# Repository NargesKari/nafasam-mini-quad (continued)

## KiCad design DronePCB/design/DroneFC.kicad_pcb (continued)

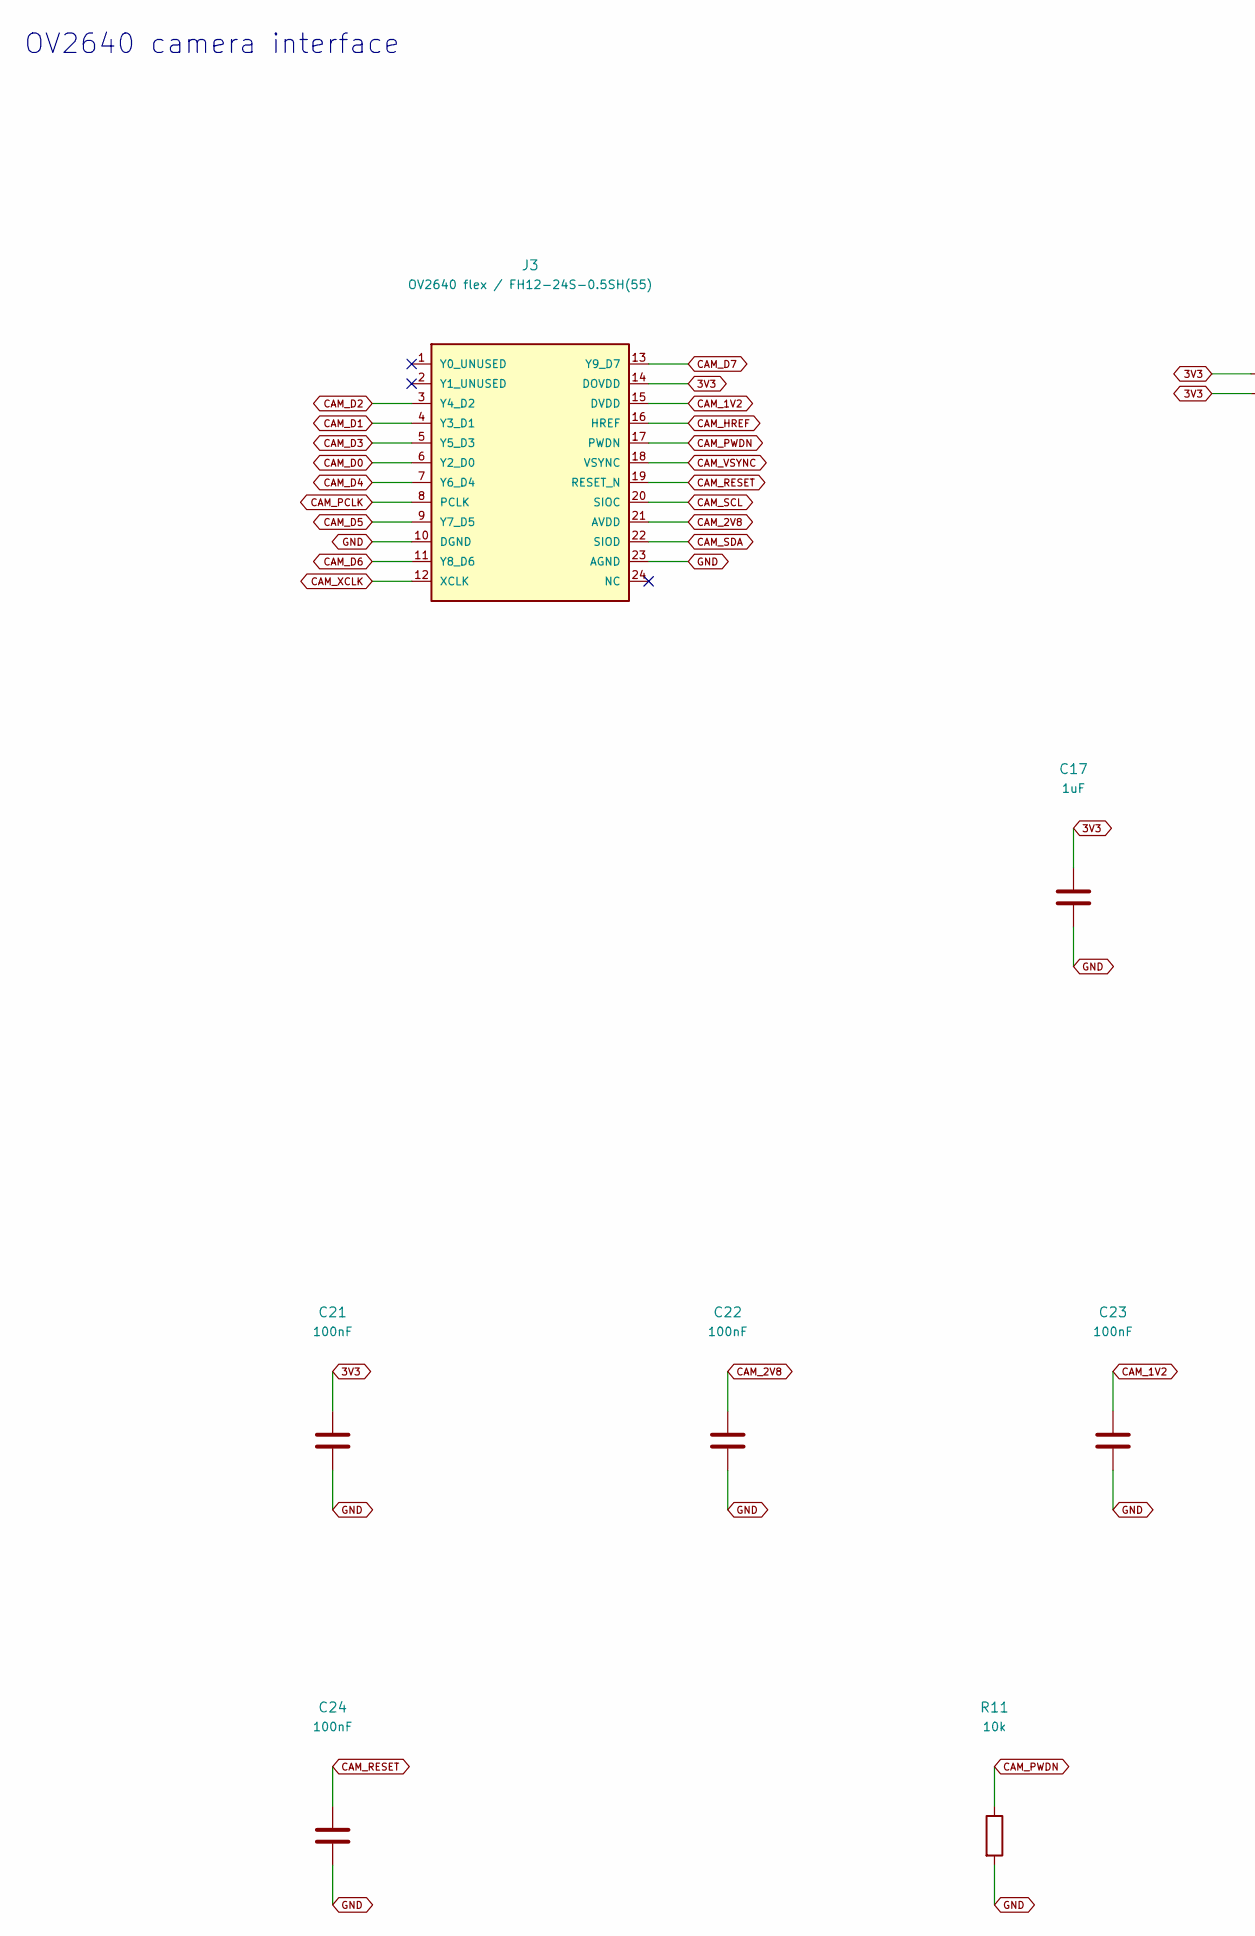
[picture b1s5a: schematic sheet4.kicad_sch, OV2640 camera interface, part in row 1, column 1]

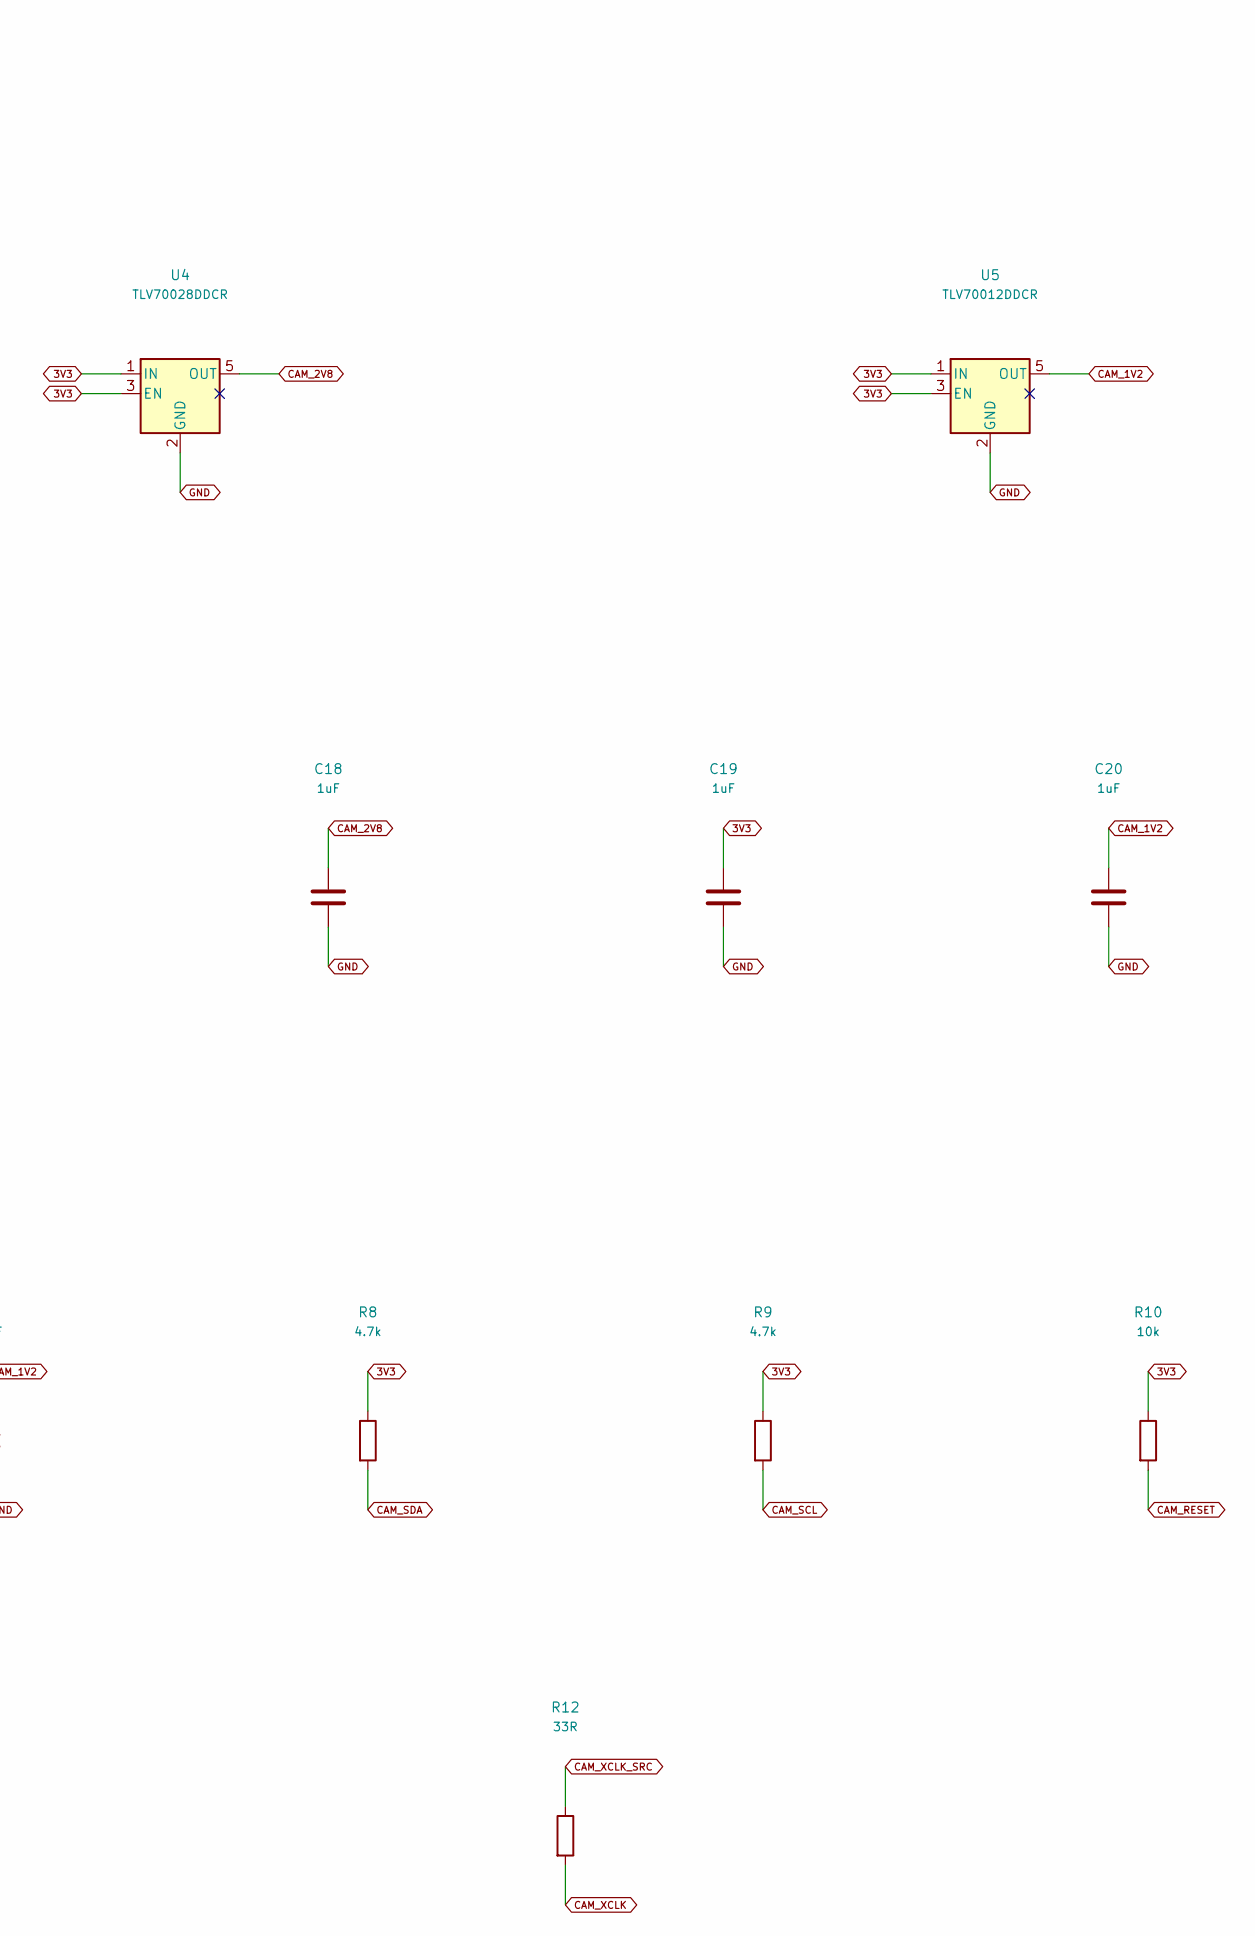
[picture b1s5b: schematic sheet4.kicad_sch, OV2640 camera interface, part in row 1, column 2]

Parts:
C17, C18, C19, C20: 1uF; C_0402_1005Metric
C21, C22, C23, C24: 100nF; C_0402_1005Metric
J3: OV2640 flex / FH12-24S-0.5SH(55); Hirose_FH12-24S-0.5SH_1x24-1MP_P0.50mm_Horizontal
R8, R9: 4.7k; R_0402_1005Metric
R10, R11: 10k; R_0402_1005Metric
R12: 33R; R_0402_1005Metric
U4: TLV70028DDCR; SOT-23-5
U5: TLV70012DDCR; SOT-23-5

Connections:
3V3: C17.1, C19.1, C21.1, J3.14 (DOVDD), R8.1, R9.1, R10.1, U4.1 (IN), U4.3 (EN), U5.1 (IN), U5.3 (EN); also elsewhere on the board
CAM_1V2: C20.1, C23.1, J3.15 (DVDD), U5.5 (OUT)
CAM_2V8: C18.1, C22.1, J3.21 (AVDD), U4.5 (OUT)
CAM_D0: J3.6 (Y2_D0); also elsewhere on the board
CAM_D1: J3.4 (Y3_D1); also elsewhere on the board
CAM_D2: J3.3 (Y4_D2); also elsewhere on the board
CAM_D3: J3.5 (Y5_D3); also elsewhere on the board
CAM_D4: J3.7 (Y6_D4); also elsewhere on the board
CAM_D5: J3.9 (Y7_D5); also elsewhere on the board
CAM_D6: J3.11 (Y8_D6); also elsewhere on the board
CAM_D7: J3.13 (Y9_D7); also elsewhere on the board
CAM_HREF: J3.16 (HREF); also elsewhere on the board
CAM_PCLK: J3.8 (PCLK); also elsewhere on the board
CAM_PWDN: J3.17 (PWDN), R11.1; also elsewhere on the board
CAM_RESET: C24.1, J3.19 (RESET_N), R10.2
CAM_SCL: J3.20 (SIOC), R9.2; also elsewhere on the board
CAM_SDA: J3.22 (SIOD), R8.2; also elsewhere on the board
CAM_VSYNC: J3.18 (VSYNC); also elsewhere on the board
CAM_XCLK: J3.12 (XCLK), R12.2
CAM_XCLK_SRC: R12.1; also elsewhere on the board
GND: C17.2, C18.2, C19.2, C20.2, C21.2, C22.2, C23.2, C24.2, J3.10 (DGND), J3.23 (AGND), R11.2, U4.2 (GND), U5.2 (GND); also elsewhere on the board

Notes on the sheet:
OV2640 camera interface

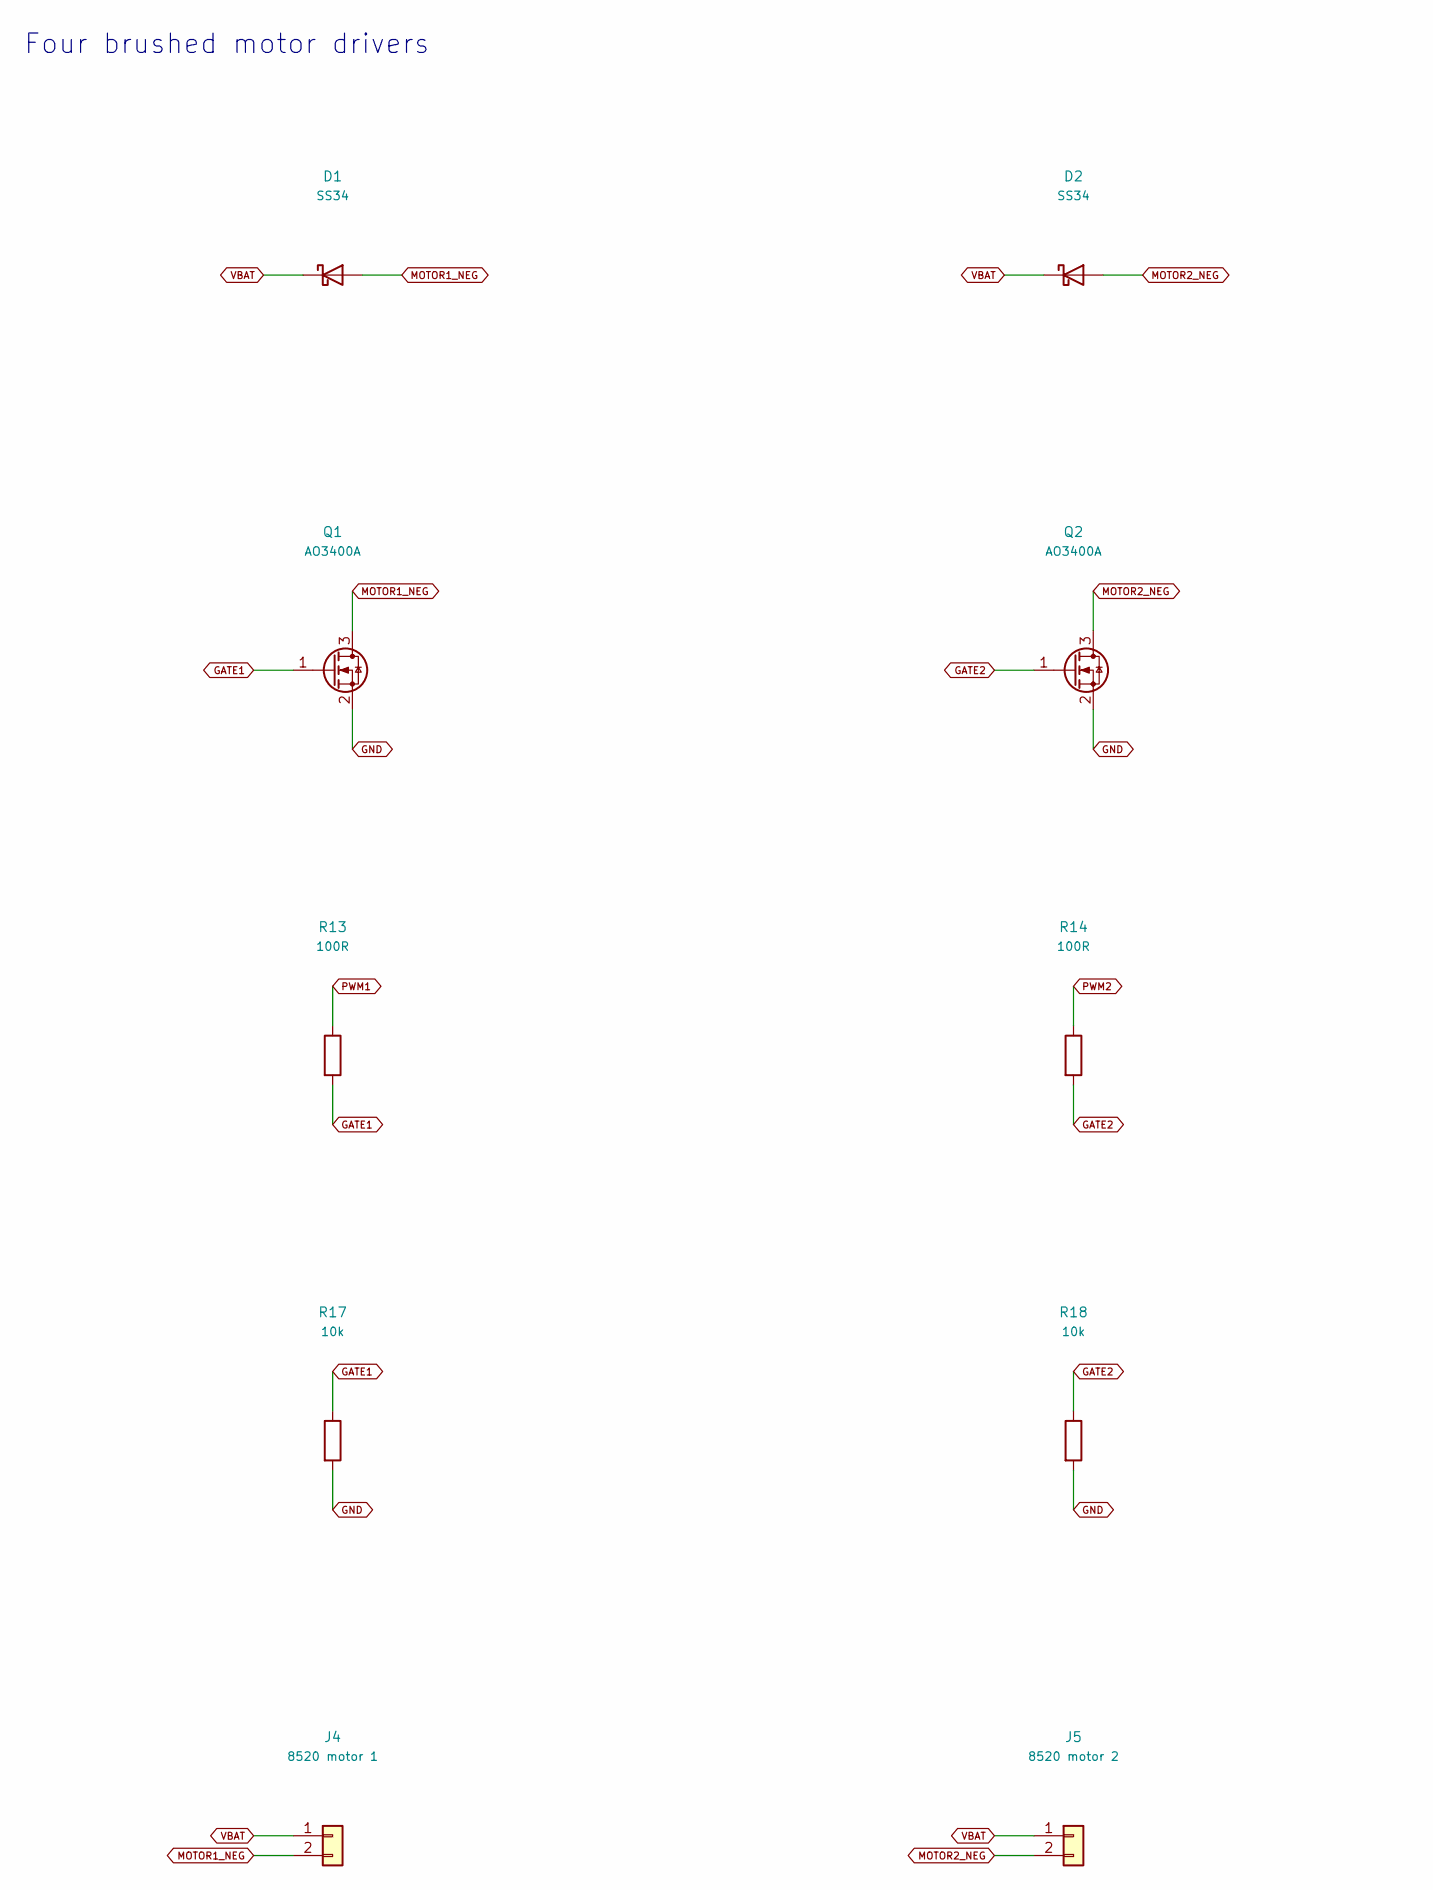
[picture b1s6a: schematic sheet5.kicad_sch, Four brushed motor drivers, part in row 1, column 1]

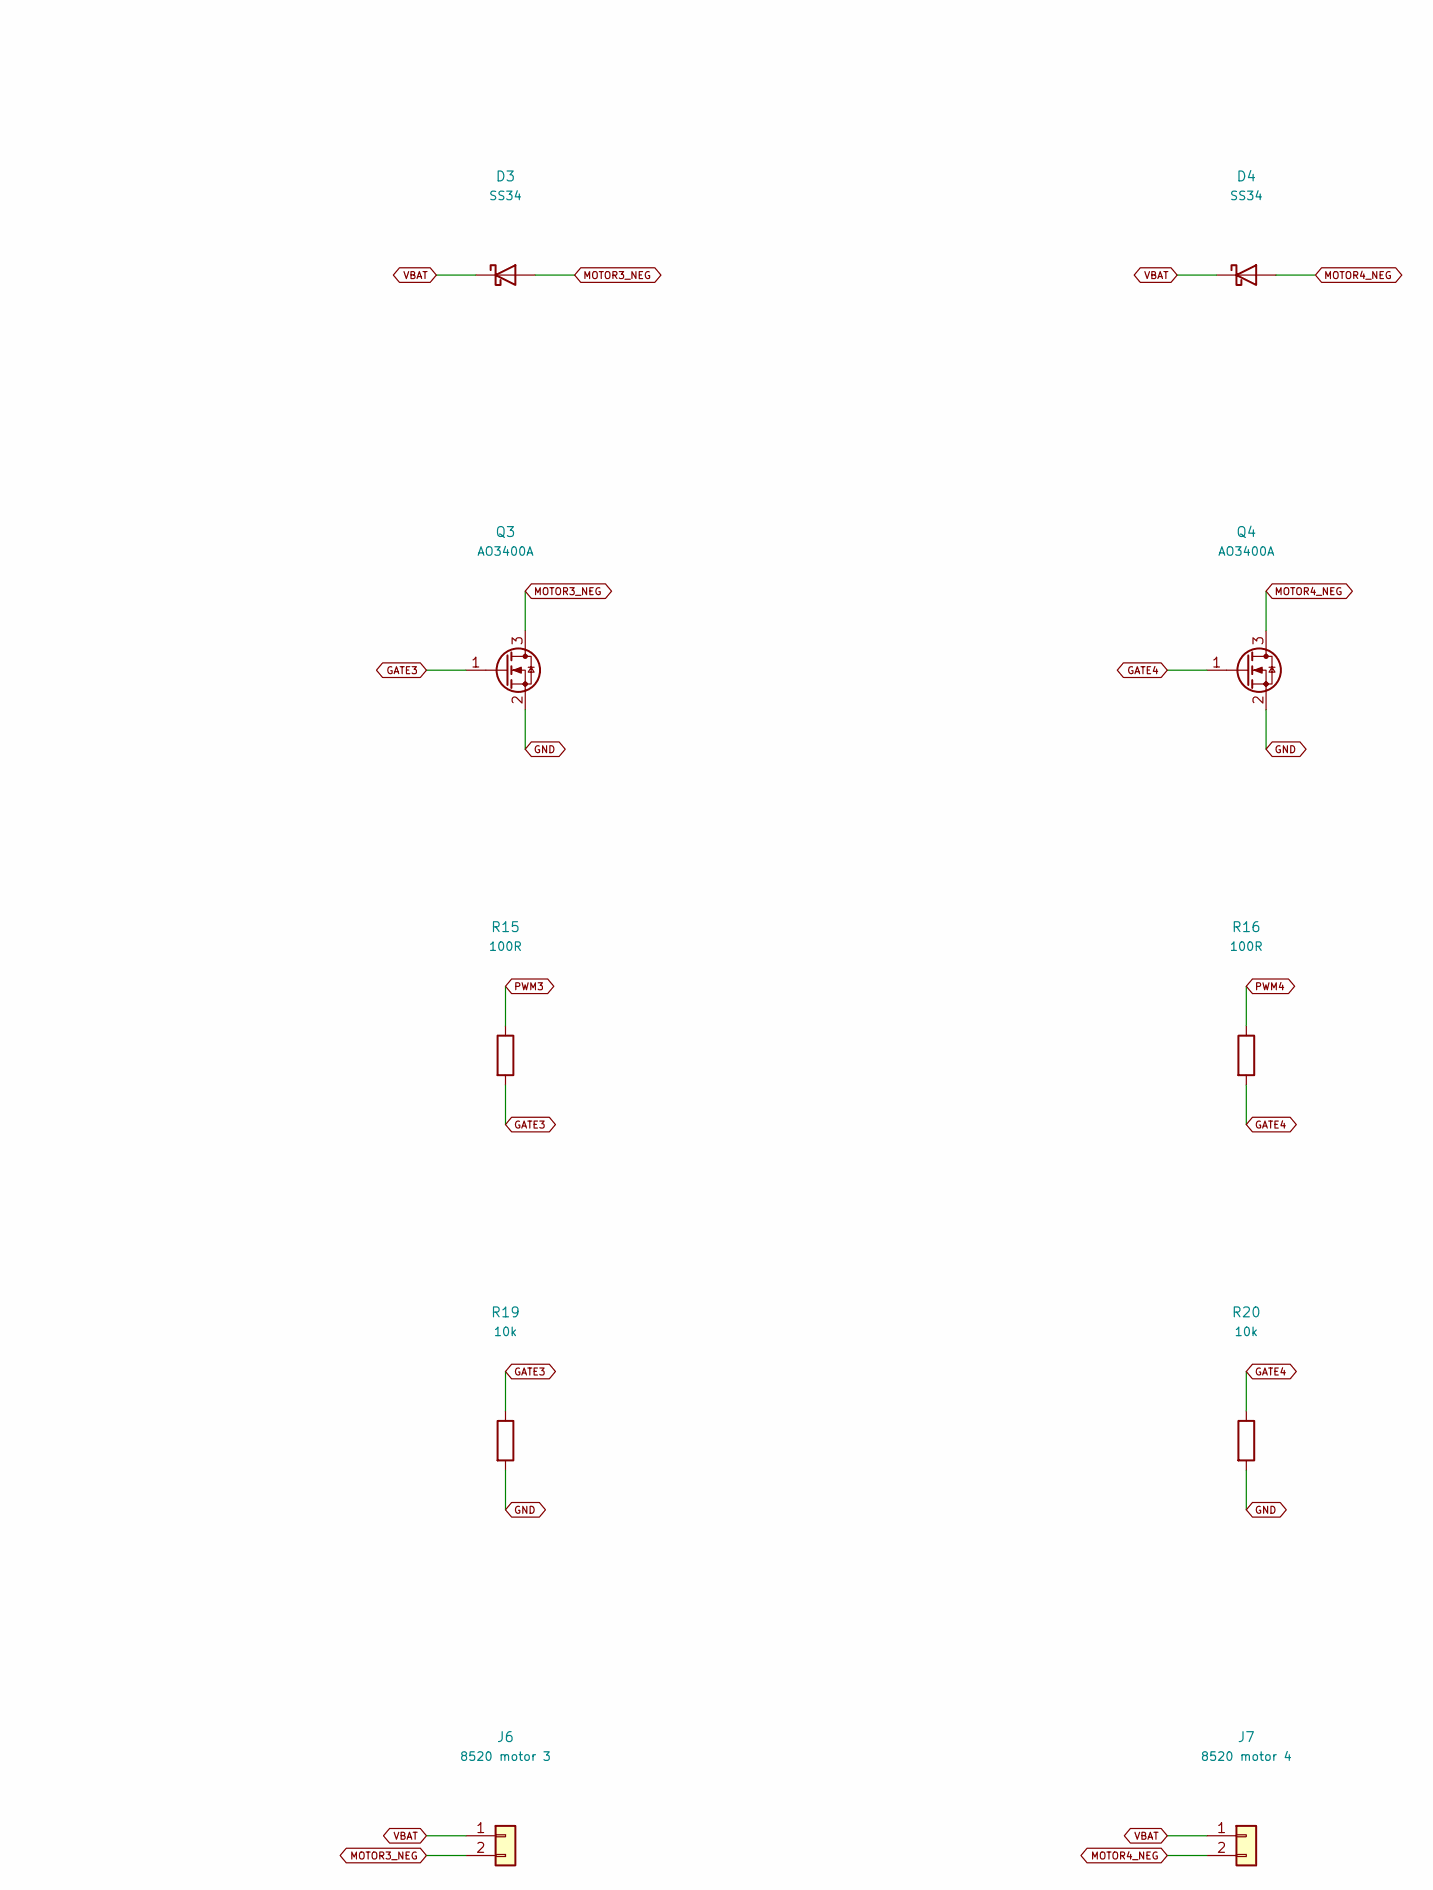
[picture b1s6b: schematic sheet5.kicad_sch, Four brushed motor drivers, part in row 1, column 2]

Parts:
D1, D2, D3, D4: SS34; D_SMA
J4: 8520 motor 1; Motor_2
J5: 8520 motor 2; Motor_2
J6: 8520 motor 3; Motor_2
J7: 8520 motor 4; Motor_2
Q1, Q2, Q3, Q4: AO3400A; SOT-23
R13, R14, R15, R16: 100R; R_0402_1005Metric
R17, R18, R19, R20: 10k; R_0402_1005Metric

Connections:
GATE1: Q1.1 (G), R13.2, R17.1
GATE2: Q2.1 (G), R14.2, R18.1
GATE3: Q3.1 (G), R15.2, R19.1
GATE4: Q4.1 (G), R16.2, R20.1
GND: Q1.2 (S), Q2.2 (S), Q3.2 (S), Q4.2 (S), R17.2, R18.2, R19.2, R20.2; also elsewhere on the board
MOTOR1_NEG: D1.2 (A), J4.2, Q1.3 (D)
MOTOR2_NEG: D2.2 (A), J5.2, Q2.3 (D)
MOTOR3_NEG: D3.2 (A), J6.2, Q3.3 (D)
MOTOR4_NEG: D4.2 (A), J7.2, Q4.3 (D)
PWM1: R13.1; also elsewhere on the board
PWM2: R14.1; also elsewhere on the board
PWM3: R15.1; also elsewhere on the board
PWM4: R16.1; also elsewhere on the board
VBAT: D1.1 (K), D2.1 (K), D3.1 (K), D4.1 (K), J4.1, J5.1, J6.1, J7.1; also elsewhere on the board

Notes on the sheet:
Four brushed motor drivers

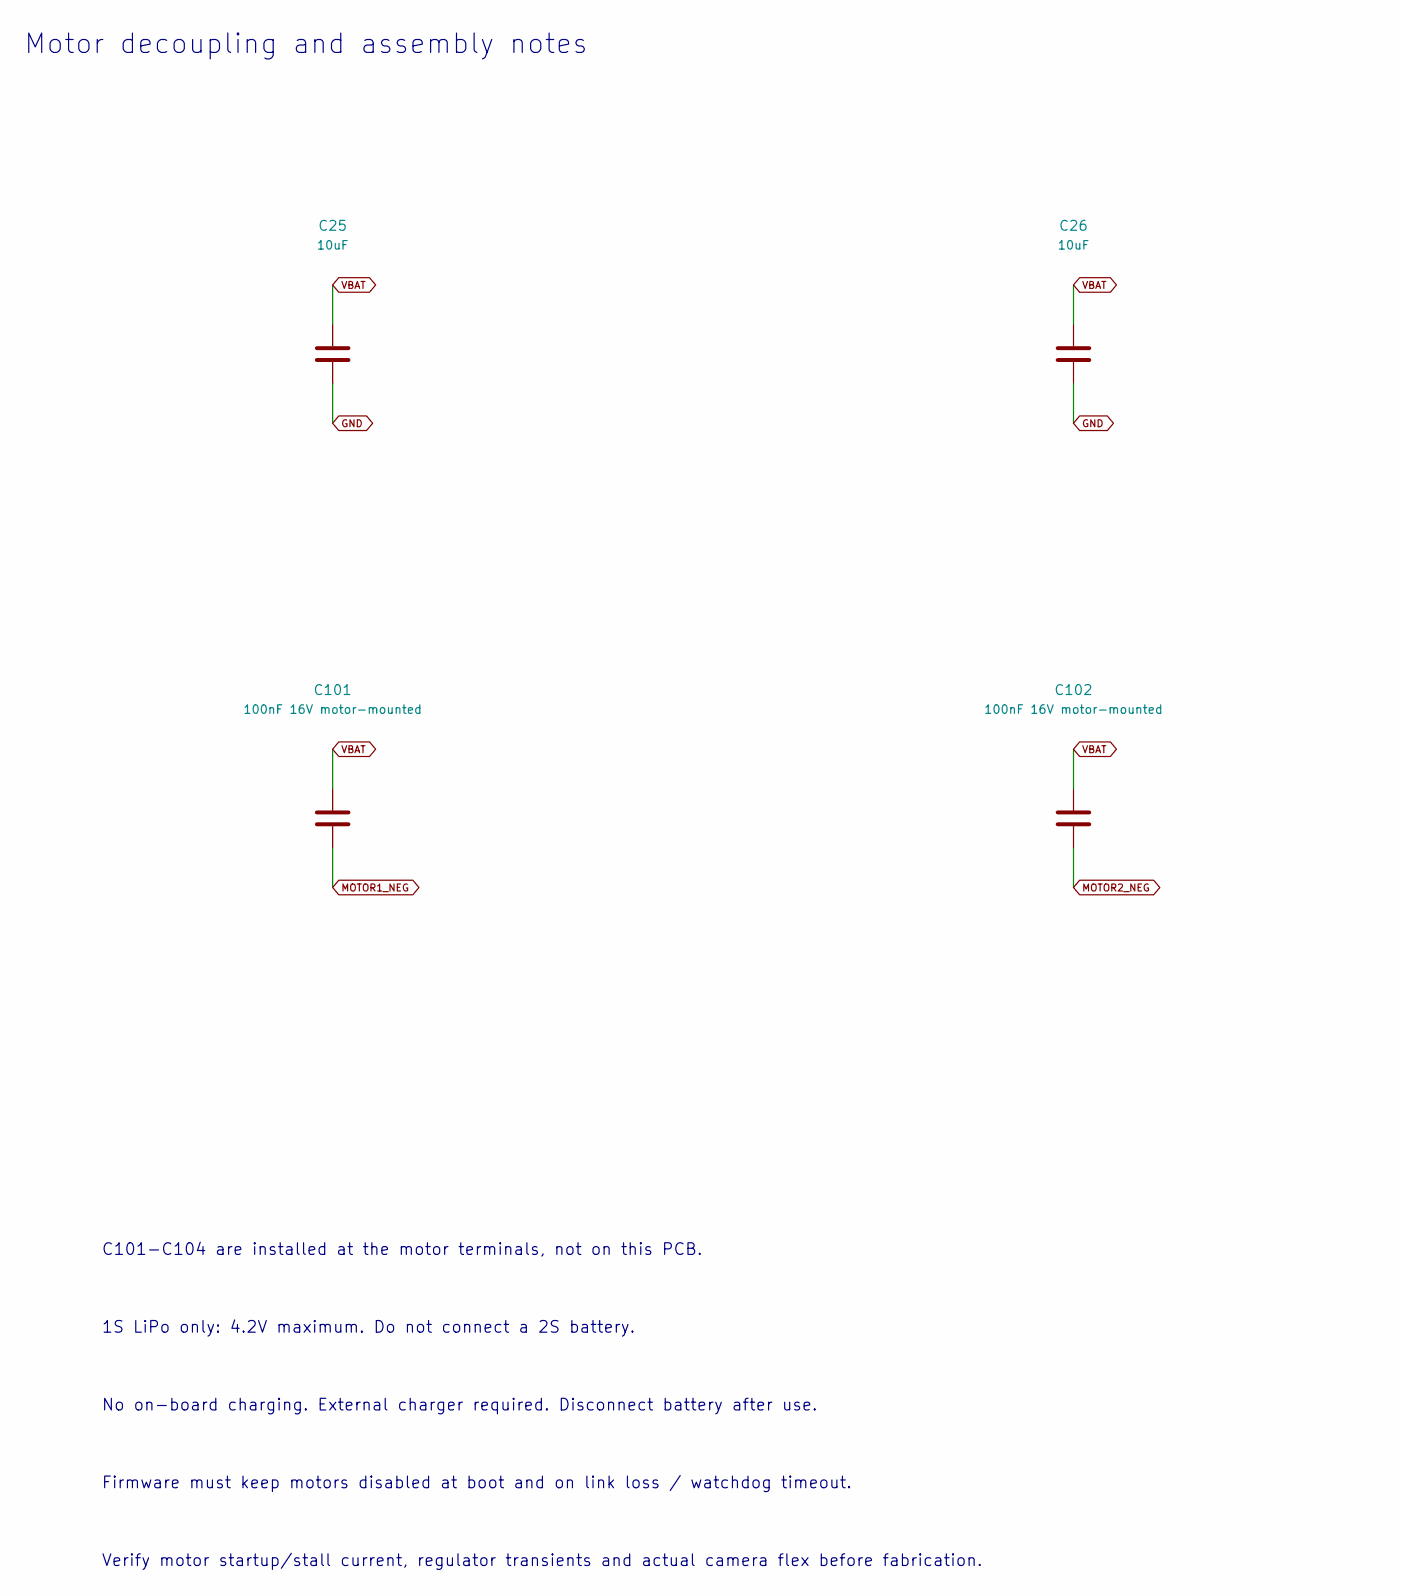
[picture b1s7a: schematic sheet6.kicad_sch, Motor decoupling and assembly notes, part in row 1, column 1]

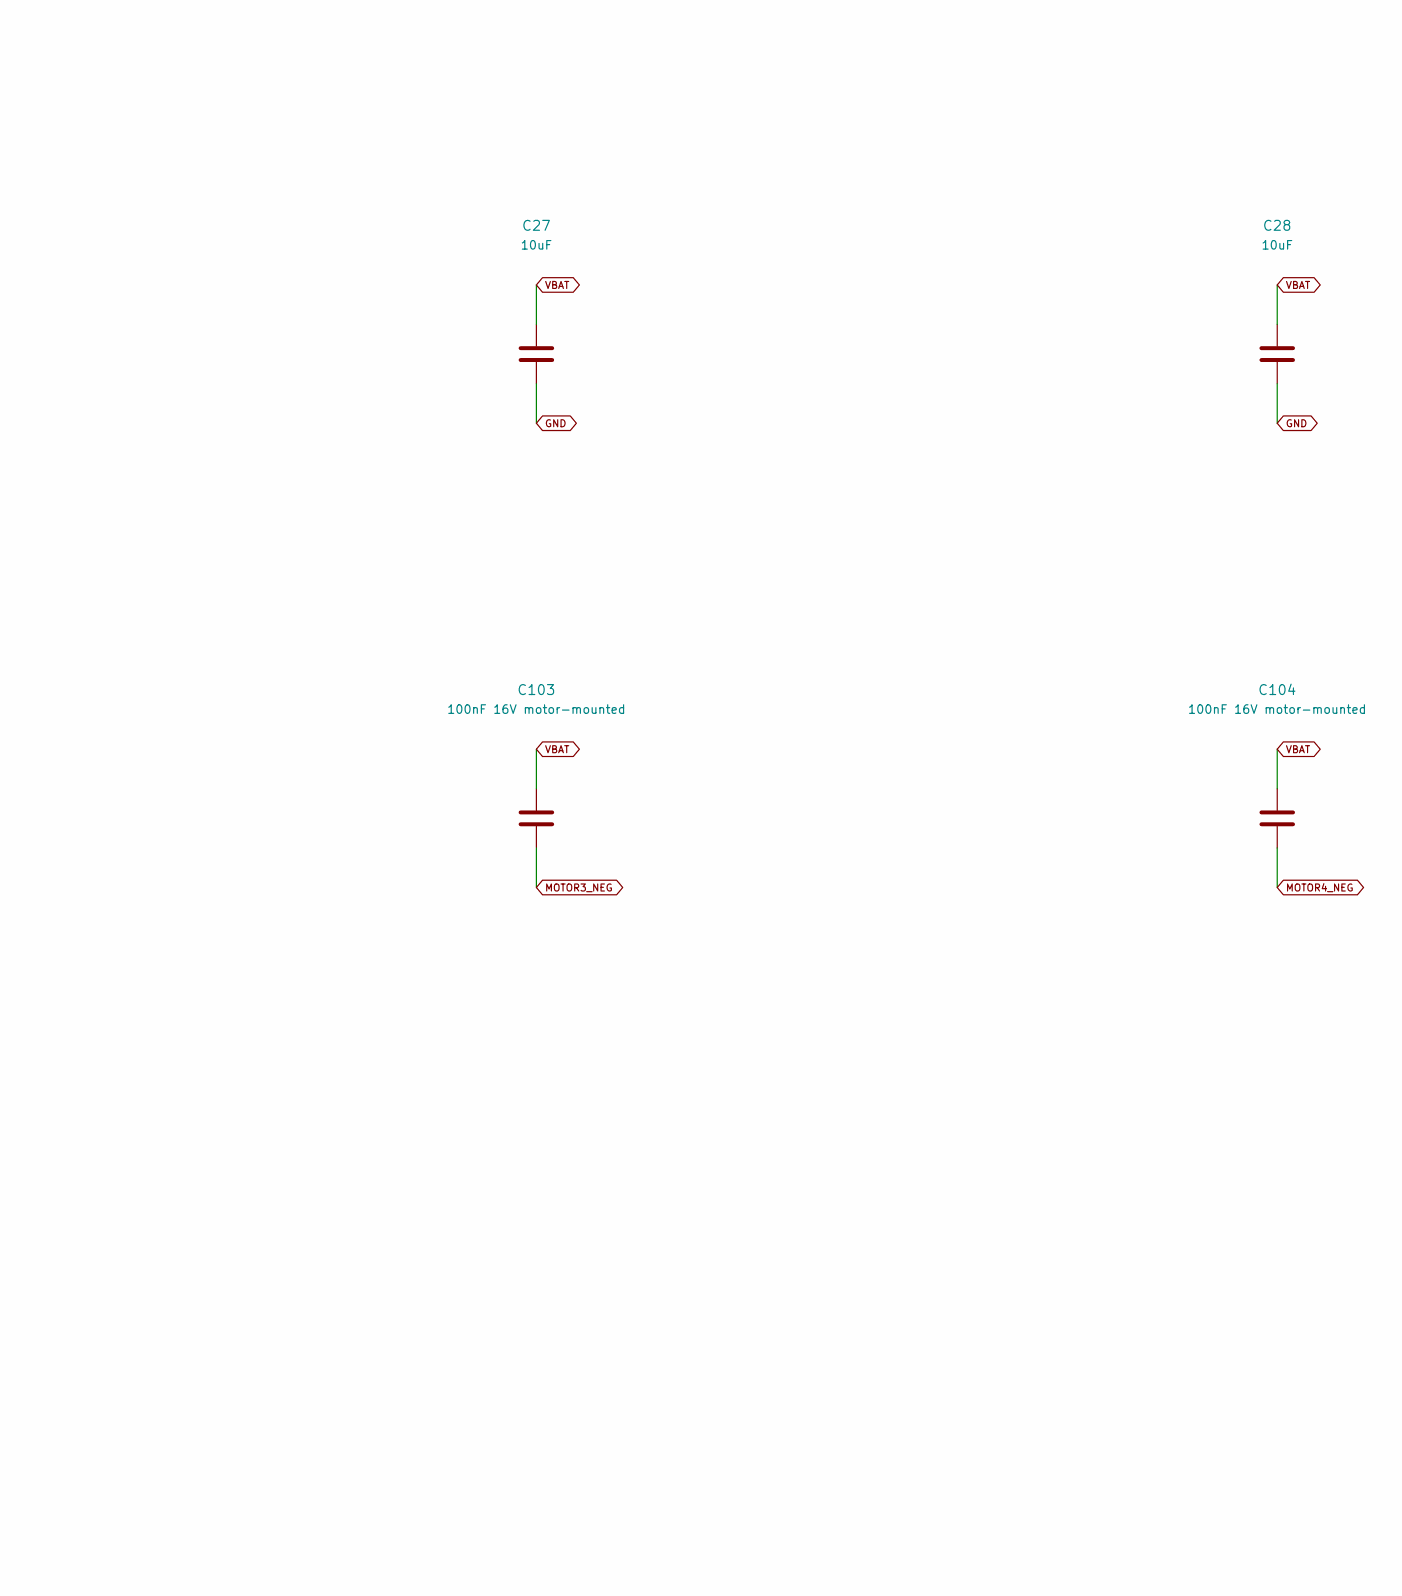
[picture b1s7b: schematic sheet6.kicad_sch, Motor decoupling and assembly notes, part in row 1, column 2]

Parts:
C25, C26, C27, C28: 10uF; C_0603_1608Metric
C101, C102, C103, C104: 100nF 16V motor-mounted

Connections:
GND: C25.2, C26.2, C27.2, C28.2; also elsewhere on the board
VBAT: C25.1, C26.1, C27.1, C28.1, C101.1, C102.1, C103.1, C104.1; also elsewhere on the board

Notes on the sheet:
Motor decoupling and assembly notes
C101-C104 are installed at the motor terminals, not on this PCB.
1S LiPo only: 4.2V maximum. Do not connect a 2S battery.
No on-board charging. External charger required. Disconnect battery after use.
Firmware must keep motors disabled at boot and on link loss / watchdog timeout.
Verify motor startup/stall current, regulator transients and actual camera flex before fabrication.

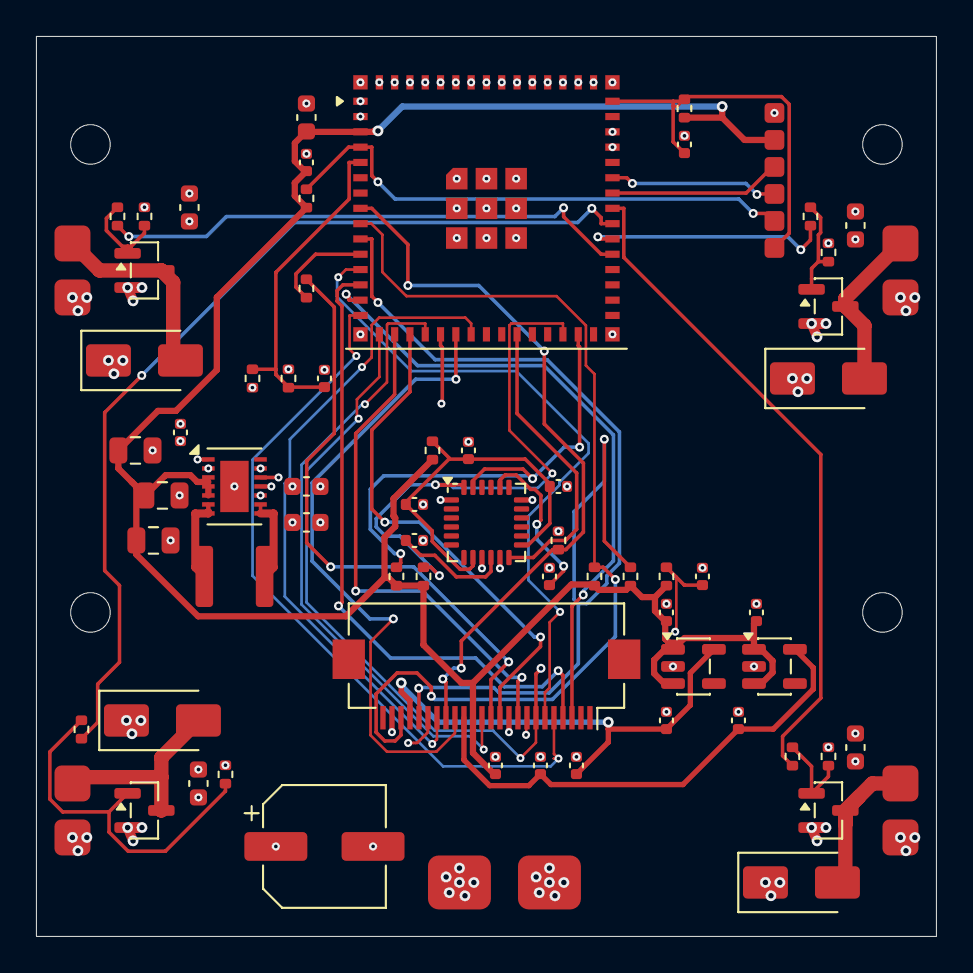
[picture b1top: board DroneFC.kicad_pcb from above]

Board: 4 copper layers, 50.0 x 50.0 mm, 73 parts (0 on the bottom side), 47 nets.

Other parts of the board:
H103103, H103147, H147103, H147147: MountingHole_2.2mm_M2

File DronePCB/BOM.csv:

Reference,Value_or_MPN,Footprint,On_PCB,Notes
U1,ESP32-S3-MINI-1-N4R2,RF_Module:ESP32-S2-MINI-1,True,4MB flash / 2MB PSRAM; module antenna extends beyond top board edge
C1,10uF,Capacitor_SMD:C_0603_1608Metric,True,"X7R, 10V; use specified voltage where marked"
C2,100nF,Capacitor_SMD:C_0402_1005Metric,True,"X7R, 10V; use specified voltage where marked"
R1,10k,Resistor_SMD:R_0402_1005Metric,True,"1%, 0402"
C3,1uF,Capacitor_SMD:C_0402_1005Metric,True,"X7R, 10V; use specified voltage where marked"
R2,10k,Resistor_SMD:R_0402_1005Metric,True,"1%, 0402"
J1,3.3V UART programmer pads,Drone:Programming_6,True,External programmer: 3.3V logic only; pin2 reference only with battery attached
R3,100k,Resistor_SMD:R_0402_1005Metric,True,"1%, 0402"
R4,100k,Resistor_SMD:R_0402_1005Metric,True,"1%, 0402"
C4,100nF,Capacitor_SMD:C_0402_1005Metric,True,"X7R, 10V; use specified voltage where marked"
U2,TPS63021DSJR,Drone:TI_DSJ14_TPS63021,True,Fixed3.3V; power-save mode; 1A electronics design target at VBAT>=3.0V subject to bench testing
L1,1.5uH XFL4020-152MEC,Drone:XFL4020,True,Coilcraft reference inductor; confirm exact suffix and DCR at sourcing
C5,10uF,Capacitor_SMD:C_0603_1608Metric,True,"X7R, 10V; use specified voltage where marked"
C6,10uF,Capacitor_SMD:C_0603_1608Metric,True,"X7R, 10V; use specified voltage where marked"
C7,100nF,Capacitor_SMD:C_0402_1005Metric,True,"X7R, 10V; use specified voltage where marked"
C8,22uF,Capacitor_SMD:C_0805_2012Metric,True,X5R 10V; verify effective capacitance under DC bias
C9,22uF,Capacitor_SMD:C_0805_2012Metric,True,X5R 10V; verify effective capacitance under DC bias
C10,22uF,Capacitor_SMD:C_0805_2012Metric,True,X5R 10V; verify effective capacitance under DC bias
J2,1S LiPo 700mAh 20C,Drone:Battery_2,True,Direct solder pads; no charger or reverse-polarity protection; disconnect battery when unused
C11,220uF 10V,Capacitor_SMD:CP_Elec_6.3x5.8,True,Low ESR aluminum/polymer; ripple-current rating >=1A; final exact part depends on sourcing
U3,MPU-6050,Sensor_Motion:InvenSense_QFN-24_4x4mm_P0.5mm,True,"I2C address0x68; use genuine bare chip, orientation must be calibrated in firmware"
R5,10R,Resistor_SMD:R_0402_1005Metric,True,"1%, 0402"
C12,1uF,Capacitor_SMD:C_0402_1005Metric,True,"X7R, 10V; use specified voltage where marked"
C13,100nF,Capacitor_SMD:C_0402_1005Metric,True,"X7R, 10V; use specified voltage where marked"
C14,10nF,Capacitor_SMD:C_0402_1005Metric,True,"X7R, 10V; use specified voltage where marked"
C15,100nF,Capacitor_SMD:C_0402_1005Metric,True,"X7R, 10V; use specified voltage where marked"
C16,2.2nF 50V,Capacitor_SMD:C_0402_1005Metric,True,X7R 50V +/-10%; charge pump capacitor
R6,4.7k,Resistor_SMD:R_0402_1005Metric,True,"1%, 0402"
R7,4.7k,Resistor_SMD:R_0402_1005Metric,True,"1%, 0402"
J3,OV2640 flex / FH12-24S-0.5SH(55),Connector_FFC-FPC:Hirose_FH12-24S-0.5SH_1x24-1MP_P0.50mm_Horizontal,True,"ONLY pin-compatible 24pin0.5mm OV2640 flex; bottom-contact connector, confirm flex contact side/length before purchase"
U4,TLV70028DDCR,Package_TO_SOT_SMD:SOT-23-5,True,"2.8V analog camera rail,200mA"
U5,TLV70012DDCR,Package_TO_SOT_SMD:SOT-23-5,True,"1.2V core camera rail,200mA"
C17,1uF,Capacitor_SMD:C_0402_1005Metric,True,"X7R, 10V; use specified voltage where marked"
C18,1uF,Capacitor_SMD:C_0402_1005Metric,True,"X7R, 10V; use specified voltage where marked"
C19,1uF,Capacitor_SMD:C_0402_1005Metric,True,"X7R, 10V; use specified voltage where marked"
C20,1uF,Capacitor_SMD:C_0402_1005Metric,True,"X7R, 10V; use specified voltage where marked"
C21,100nF,Capacitor_SMD:C_0402_1005Metric,True,"X7R, 10V; use specified voltage where marked"
C22,100nF,Capacitor_SMD:C_0402_1005Metric,True,"X7R, 10V; use specified voltage where marked"
C23,100nF,Capacitor_SMD:C_0402_1005Metric,True,"X7R, 10V; use specified voltage where marked"
R8,4.7k,Resistor_SMD:R_0402_1005Metric,True,"1%, 0402"
R9,4.7k,Resistor_SMD:R_0402_1005Metric,True,"1%, 0402"
R10,10k,Resistor_SMD:R_0402_1005Metric,True,"1%, 0402"
C24,100nF,Capacitor_SMD:C_0402_1005Metric,True,"X7R, 10V; use specified voltage where marked"
R11,10k,Resistor_SMD:R_0402_1005Metric,True,"1%, 0402"
R12,33R,Resistor_SMD:R_0402_1005Metric,True,Source series damping; tune with scope
Q1,AO3400A,Package_TO_SOT_SMD:SOT-23,True,SOT23 G1/S2/D3; verify stall current and heating with actual prop
R13,100R,Resistor_SMD:R_0402_1005Metric,True,"1%, 0402"
R17,10k,Resistor_SMD:R_0402_1005Metric,True,"1%, 0402"
D1,SS34,Diode_SMD:D_SMA,True,3A40V Schottky flyback; cathode pad1 to VBAT
J4,8520 motor 1,Drone:Motor_2,True,Direct motor wire solder pads; motor body not on PCB
C25,10uF,Capacitor_SMD:C_0603_1608Metric,True,"X7R, 10V; use specified voltage where marked"
C101,100nF 16V motor-mounted,,False,"Solder directly across motor terminals; included in BOM, off-board"
Q2,AO3400A,Package_TO_SOT_SMD:SOT-23,True,SOT23 G1/S2/D3; verify stall current and heating with actual prop
R14,100R,Resistor_SMD:R_0402_1005Metric,True,"1%, 0402"
R18,10k,Resistor_SMD:R_0402_1005Metric,True,"1%, 0402"
D2,SS34,Diode_SMD:D_SMA,True,3A40V Schottky flyback; cathode pad1 to VBAT
J5,8520 motor 2,Drone:Motor_2,True,Direct motor wire solder pads; motor body not on PCB
C26,10uF,Capacitor_SMD:C_0603_1608Metric,True,"X7R, 10V; use specified voltage where marked"
C102,100nF 16V motor-mounted,,False,"Solder directly across motor terminals; included in BOM, off-board"
Q3,AO3400A,Package_TO_SOT_SMD:SOT-23,True,SOT23 G1/S2/D3; verify stall current and heating with actual prop
R15,100R,Resistor_SMD:R_0402_1005Metric,True,"1%, 0402"
R19,10k,Resistor_SMD:R_0402_1005Metric,True,"1%, 0402"
D3,SS34,Diode_SMD:D_SMA,True,3A40V Schottky flyback; cathode pad1 to VBAT
J6,8520 motor 3,Drone:Motor_2,True,Direct motor wire solder pads; motor body not on PCB
C27,10uF,Capacitor_SMD:C_0603_1608Metric,True,"X7R, 10V; use specified voltage where marked"
C103,100nF 16V motor-mounted,,False,"Solder directly across motor terminals; included in BOM, off-board"
Q4,AO3400A,Package_TO_SOT_SMD:SOT-23,True,SOT23 G1/S2/D3; verify stall current and heating with actual prop
R16,100R,Resistor_SMD:R_0402_1005Metric,True,"1%, 0402"
R20,10k,Resistor_SMD:R_0402_1005Metric,True,"1%, 0402"
D4,SS34,Diode_SMD:D_SMA,True,3A40V Schottky flyback; cathode pad1 to VBAT
J7,8520 motor 4,Drone:Motor_2,True,Direct motor wire solder pads; motor body not on PCB
C28,10uF,Capacitor_SMD:C_0603_1608Metric,True,"X7R, 10V; use specified voltage where marked"
C104,100nF 16V motor-mounted,,False,"Solder directly across motor terminals; included in BOM, off-board"
